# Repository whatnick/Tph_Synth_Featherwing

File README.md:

# 3-Phase ELV synthesizer using DAC and Opamps

This is an extra-low-voltage (ELV) FeatherWing using an MCP4728 four-channel,
12-bit I2C DAC with filtering and op-amp signal conditioning. The schematic
exposes three voltage outputs and one Howland current output, not three
independent voltage/current pairs. Host timing, output range and accuracy
require hardware validation; this is not a mains power source or a certified
meter calibrator.

## Background and availability

The original prototype is described in
[Simulating 3-phase AC for Energy Monitor testing (October 2017)](https://whatnicklife.blogspot.com/2017/10/simulating-3-phase-ac-for-energy.html).
It used a Teensy 3.2, MCP4728 and op-amp conditioning to test energy monitors.
Those historical results do not qualify the current v0.4 hardware.

The [Tindie listing](https://www.tindie.com/products/whatnick/3-phase-ac-synthesizer/)
was US$50 and out of stock when checked on 2026-11-08. See the
[market, lab TCO and NILM replay assessment](doc/synthesis-business-case.md)
for competing equipment, cost assumptions, research references and the
limitations of appliance-signature injection.
The matching Tindie blog-link update is tracked in
[issue #7](https://github.com/whatnick/Tph_Synth_Featherwing/issues/7);
publishing it requires authenticated seller access.

## KiCad 10 design

Revision **v0.4 (2026-10-28)** is maintained in
`Tph_Synth_Featherwing\Tph_Synth_Featherwing.kicad_pro`. Open that project and
its root schematic rather than treating the hierarchical sheets as separate
projects. The revision is also printed on the PCB bottom silkscreen.

The project-local symbol and footprint tables resolve the converted libraries,
board-edge silkscreen variants and existing `3dmodels` assets. Keep these
directories together with the project and install the standard KiCad 10
symbol, footprint and 3D-model libraries.

From the repository root, validate with KiCad 10's `kicad-cli` on `PATH`:

```powershell
kicad-cli sch erc .\Tph_Synth_Featherwing\Tph_Synth_Featherwing.kicad_sch --severity-all --exit-code-violations
kicad-cli pcb drc .\Tph_Synth_Featherwing\Tph_Synth_Featherwing.kicad_pcb --severity-all --schematic-parity --exit-code-violations
```

Both checks pass with zero violations, unconnected items or schematic-parity
mismatches. All 515 existing tracks/vias and component placement are preserved.
The Default and Power netclasses use 0.15 mm clearance; silkscreen-edge checking
is enabled. See [the v0.4 schematic](doc/v0.4/schematic.pdf) and
[top](doc/v0.4/board-top.png)/[bottom](doc/v0.4/board-bottom.png) renders and a
[populated STEP turntable](doc/v0.4/board-turntable.mp4) (Feather headers are
DNP and not shown). Recreate it by exporting a populated STEP with
`kicad-cli pcb export step --subst-models --include-tracks --include-pads
--include-silkscreen --include-soldermask`, converting it to GLB with the
`cascadio` Python package, then running
`blender -b --factory-startup -P scripts/render_turntable.py -- board.glb out.mp4 150 anim`.
The exact R10 PV36W STEP was unavailable, so R10 uses the generic 3296W model.
These are visualisations, not mechanical fit certification.
These CAD checks do not replace hardware/firmware and analog-output testing.

## Manufacturing preparation

The current preparation is in `manufacturing\v0.4`. **Assembly and purchasing
are on hold**, even though the CAD checks pass. Use the freshly generated
fabrication ZIP there, not the historical `Tph_Synth_Featherwing\gerbers`,
`bom` spreadsheet or iBOM. The archive has copper, mask, silkscreen, paste and
outline Gerbers plus separate PTH/NPTH drills. The nominal outline is
51 x 58.5 mm, two copper layers, 1.6 mm board thickness. Confirm material,
copper weight, surface finish, quantity and panelization with the fabricator.
The [ten-board Elecrow PCBA request](manufacturing/elecrow-pcba-2026-11-07/quote.json),
PN `20261107105421`, was submitted on 2026-11-07 and remains Pending Quotation
on the 2026-11-08 live check. Components are unpriced; US$88 plus separately
listed US$15.94 freight is not the final turnkey price. No payment or
production approval was made. The earlier bare-PCB cart entry is historical
and its absence does not establish a complete ordering history.

Generate a new package into an empty directory using KiCad's bundled Python:

```powershell
& 'C:\Program Files\KiCad\10.0\bin\python.exe' .\scripts\prepare_manufacture.py --output .\manufacturing\v0.4-new
```

The exporter requires zero ERC, DRC, unconnected and parity findings. It derives
the BOM from schematic fields, checks SMT placements against that BOM and
records input/output SHA-256 hashes in `manifest.json`. Regenerate into a new
directory if the destination is already populated; it deliberately refuses to
mix old and new exports. `release-status.json` records every sourcing review
and release action. Positions are in millimetres using the absolute CAD origin
for Gerbers, drills and placements; bottom X is not negated. Have the assembler
verify rotations, polarity and panel tooling. THT parts are listed separately
from the SMT position file.

For [issue #3](https://github.com/whatnick/Tph_Synth_Featherwing/issues/3),
SDA, SCL, 3V3, GND, VUSB and VBAT are labelled at the Feather header pads on
both PCB sides. Back-side labels are mirrored for correct fabrication.
Silkscreen checks enforce 0.15 mm clearance; test-pad references and the U4
reference are positioned clear of other markings. Run the tests with KiCad's
bundled Python to include the PCB pin-label and silkscreen-rule checks:

```powershell
& 'C:\Program Files\KiCad\10.0\bin\python.exe' -m unittest discover -s tests -v
```

Initial legacy sourcing evidence is in `sourcing\distributor-review-2026-11-07.json`
and copied into the manufacturing package. All 21 unique legacy fitted MPNs (46 parts,
22 BOM rows) were checked in three Mouser MCP batches; DigiKey was used for
four targeted blocker/candidate lookups. Results were matched by **MPN and
manufacturer**, excluding an unrelated obsolete ROHM `LM324PWR` result.
Prices are indicative USD single-unit observations, not a quotation or landed
cost. Null Mouser lifecycle means "not stated", not "Active".

The user-approved breakout replacements are now applied to the schematic,
PCB and review BOM, including legacy `manf#` fields:

| References | Selected MPN | Ratings/package | Stocked source observed 2026-11-07 |
|---|---|---|---|
| C1-C3 | TDK `C2012X5R1V226MT000E` | 22 uF, +/-20%, 35 V, X5R, 0805 | LCSC/JLCPCB `C338080`: 56,013 |
| C4-C11/C18 | Murata `GRM21BR61H106KE43L` | 10 uF, +/-10%, 50 V, X5R, 0805 | Mouser `81-GRM21BR61H106KE3L`: 2,564; JLCPCB `C440198`: 1,065,869 |
| C12 | YAGEO `CC0603BRNPO9BN5R0` | 5 pF, +/-0.1 pF, 50 V, C0G, 0603 | Mouser `603-CC603BRNPO9BN5R0`: 2,442 |

See `sourcing\distributor-review-substitutions-2026-11-07.json` for approval,
voltage rationale and current choices; the earlier review and alternative
records are historical. No voltage rating is reduced. The intended VBAT/5 V
and +/-5 V circuits are below these ratings; external overvoltage and fault
transients have not been qualified. Copper, placement and footprint geometry
are unchanged.

Remaining release checks:

- **Capacitor performance:** the 22 uF dielectric changes from JB to X5R.
  Check effective capacitance under DC bias/temperature, boost and charge-pump
  startup/ripple/stability, and 5 pF compensation on hardware. Murata's reference
  sheet is headed General Purpose, while DigiKey labels its application Mobile
  Devices Only; use is approved for this breakout, not unrestricted production.
  Keep the manufacturer application/height checks on the release checklist.
- **Supply/packing:** the TDK exact MPN is sourced through LCSC/JLCPCB, not
  presently orderable at Mouser or DigiKey. Recheck inventory before purchase.
  Observed Mouser stock of the replacements is below one full reel; verify
  packaging with the assembler and supplier rather than assuming reel supply.
- **R10:** verify `PV36W202C01B00` body/lead geometry, pin numbering and adjustment
  access against the Bourns 3296W footprint. This is an unverified fit, not a
  demonstrated mismatch: the PCB has three collinear holes on 2.54 mm centres,
  0.8 mm drills; pins 1/2 are connected and pin 3 is unused.
  The supplied `doc/pv36.pdf` now confirms inline pitch/pin order and pin 2
  as wiper, but recommends 0.9 mm holes rather than the PCB's 0.8 mm.
  Nominal lead diameter is 0.51 +/-0.03 mm; check finished-hole tolerances
  and insertion. R10's 3296W 3D model remains a proxy, not a verified PV36W.
- **Panel-pot CAD:** R7/R8/R9/RV1 use the Bourns PTV09A-2X20F family STEP.
  Corrected its model X offset from 3.5 to 3.1 mm to align signal leads.
  All lead/tab sections fit nominal holes at board midplane, but about
  0.331 mm3 model/board intersection remains per pot near mounting features;
  verify physical seating. See `sourcing\distributor-review-pot-fit-2026-11-07.json`
  for measurements, provenance and exact-MPN model-search limitations.
- **Host interface:** Adafruit
  [3200](https://www.adafruit.com/product/3200) is an external Teensy-to-Feather
  adapter, not a component fitted at MS1. It is listed separately from the PCB
  assembly BOM. **DNP the Feather host 12-pin/16-pin headers during
  manufacture.** Users fit compatible stacking headers later to suit their
  Feather; factory header selection/stacking height is not a release blocker.
  This policy applies only to the host rows, not fitted J2/J3 connectors.
  Headers and the Teensy are excluded from factory purchasing.
- **Production quantity/packaging:** R11-R14 consume four precision resistors
  per board; the 163 units observed at Mouser cover at most 40 boards before
  spares. U4 `MCP4728-E/UN` is supplied in tubes; assembler acceptance or a
  qualified reel suffix is still required.
- All other legacy MPNs still require datasheet electrical/mechanical
  qualification and a fresh stock, packaging, price and lifecycle check before
  ordering. Bench-test power rails, I2C/DAC, analog outputs and
  the Howland current source before a production release.

`Manufacturer`, `MPN`, `Description`, `DigiKey`, `Mouser`, `Assembly`,
`SourcingStatus` and `SourcingNotes` live on the schematic symbols and are
mirrored to the PCB for parity. `DigiKey` and `Mouser` remain **search URLs**.
Separate `MouserOrderCode`, `DigiKeyOrderCode`, `LCSCOrderCode` and `DistributorChecked` fields
carry dated, exact-manufacturer MCP observations; blank DigiKey codes mean
that MPN was not checked there. These codes do not override a sourcing hold.

The harness now connects to the public **pcbparts** MCP at
`https://pcbparts.dev/mcp`. `mouser_get_part` batches up to 10 part lookups;
`digikey_get_part` checks one MPN/order code at a time. Parametric catalog
search is provided by `jlc_search`, not the distributor lookup tools.
The hosted service shares a 1,000-request/day quota per distributor; do not
retry quota errors or check the whole BOM repeatedly in DigiKey. No API keys
are needed for this hosted endpoint. Self-hosting requires your own
[DigiKey developer API](https://developer.digikey.com/) and
[Mouser Search API](https://www.mouser.com/api-search/) credentials to enable
their lookups. Keep credentials outside the repository.

## Features :
- 50/60 Hz Frequency Selector ( Possibly just do it in software).
- Pot driven voltage Setting by controlling inverting-Opamp gain.
- Modified-Howland current source to simulate current clamp output.
- Pot driven current source using a tapped potentiometer attached to DAC output.
- Adjustable AC voltage outputs from nominal +/-5 V op-amp supplies; available
  swing depends on headroom and load, and is not a +/-5 V RMS specification.
- Dual-voltage rail generation using [LM2663](https://au.element14.com/texas-instruments/lm2663mx-nopb/dc-dc-charge-pump-inverting-soic/dp/3008264) to flip 5v input to -5v.
- Boost-converter to push battery voltage (4.2v-3.7v) to 5v for non-USB power mode using [PAM2401](https://au.mouser.com/datasheet/2/115/PAM2401-347378.pdf).
- I2C DAC circuit to generate phase-shifted sine waves, as described in the
  [original prototype blog post](https://whatnicklife.blogspot.com/2017/10/simulating-3-phase-ac-for-energy.html),
  using [MCP4728](https://au.element14.com/microchip/mcp4728-e-un/ic-dac-12bit-quad-10msop/dp/1800217).
- Fully open-source schematic/pcb in KiCAD.

## Roadmap Features :
- Keep this board ELV-only; qualify output limits and provide repeatable
  low-voltage teaching and meter-front-end test procedures.
- Evaluate USB/battery power-path improvements within the ELV design envelope.
- Add I2C digital pots instead of physical pots.

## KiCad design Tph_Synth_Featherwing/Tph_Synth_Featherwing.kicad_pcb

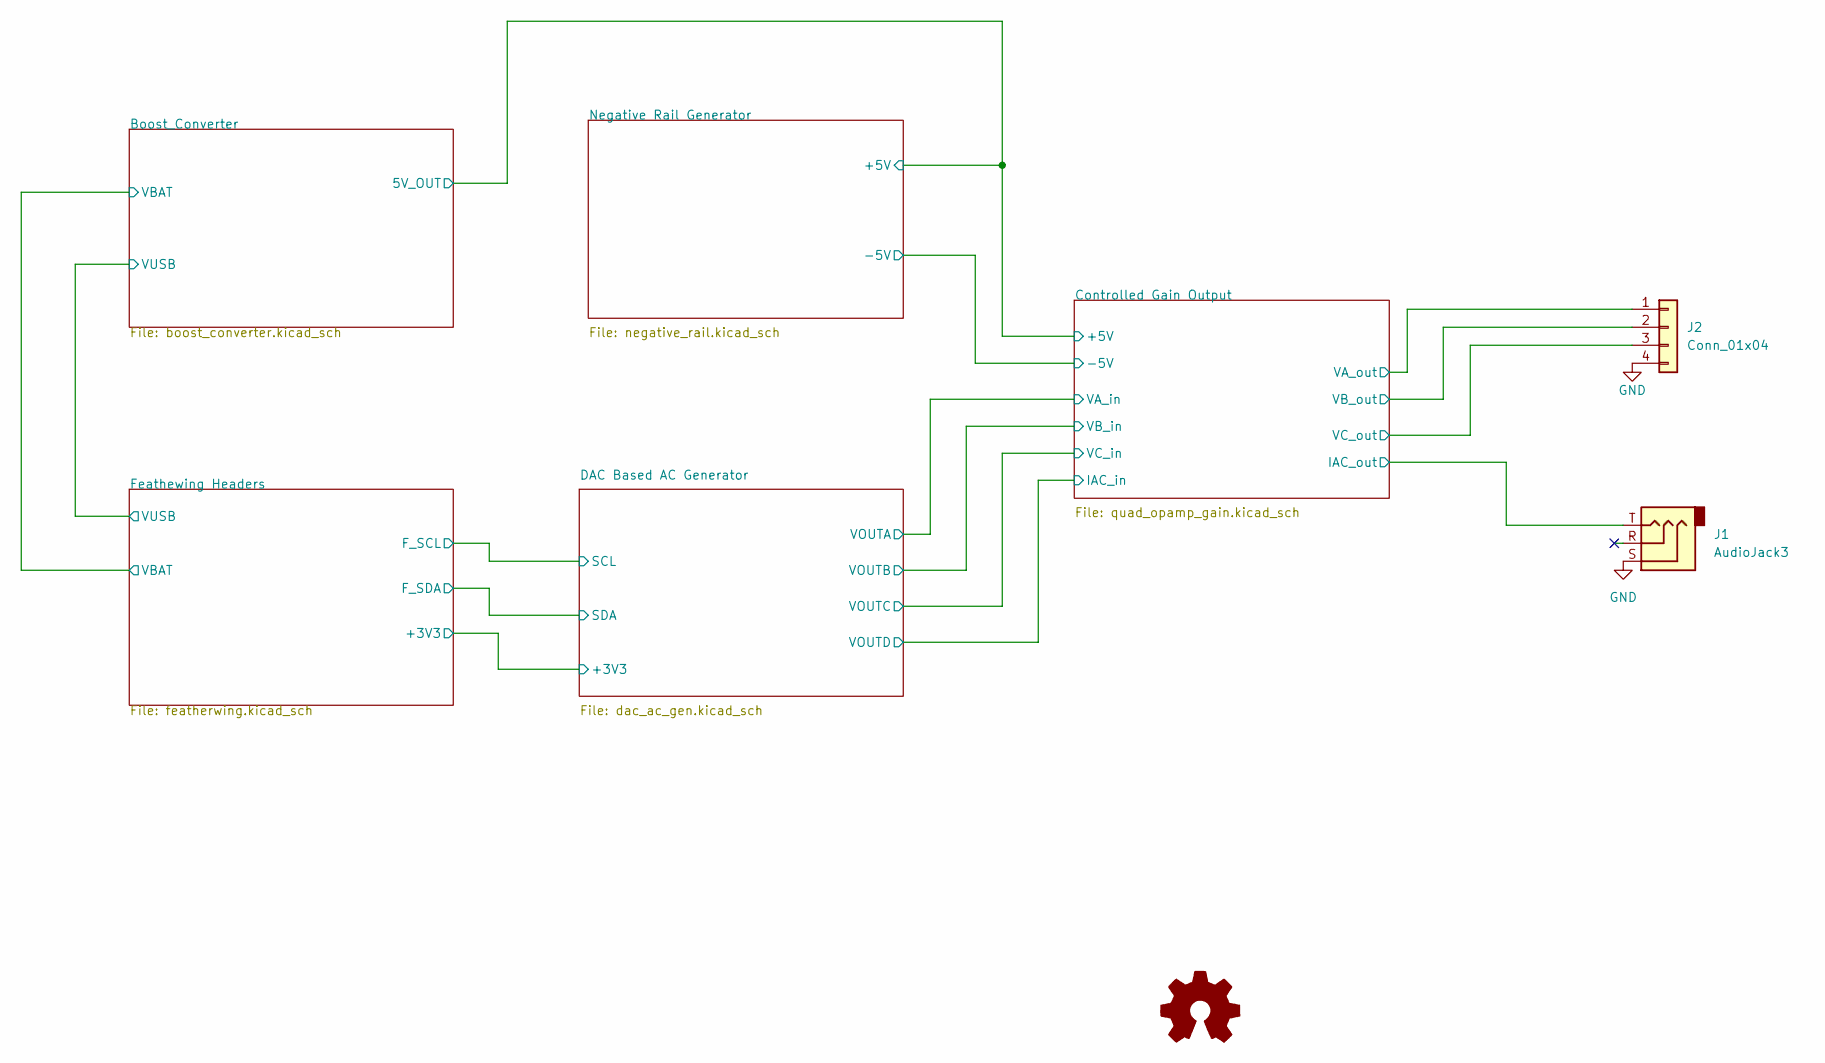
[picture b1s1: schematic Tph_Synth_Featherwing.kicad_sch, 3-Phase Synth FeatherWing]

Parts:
J1: AudioJack3; Jack_3.5mm_CUI_SJ-3523-SMT_Horizontal_EdgeMounted; MPN SJ-3523-SMT-TR; MouserOrderCode 490-SJ-3523-SMT-TR
J2: Conn_01x04; Molex_Nano-Fit_105314-xx04_2x02_P2.50mm_Horizontal_EdgeMoun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; MPN 105314-1204; MouserOrderCode 538-105314-1204
LOGO1: Logo_Open_Hardware_Small; OSHW-Logo2_7.3x6mm_SilkScreen

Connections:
/Controlled Gain Output/IAC_out: J1.T; also elsewhere on the board
/Controlled Gain Output/VA_out: J2.1; also elsewhere on the board
/Controlled Gain Output/VB_out: J2.2; also elsewhere on the board
/Controlled Gain Output/VC_out: J2.3; also elsewhere on the board
GND: J1.S, J2.4; also elsewhere on the board

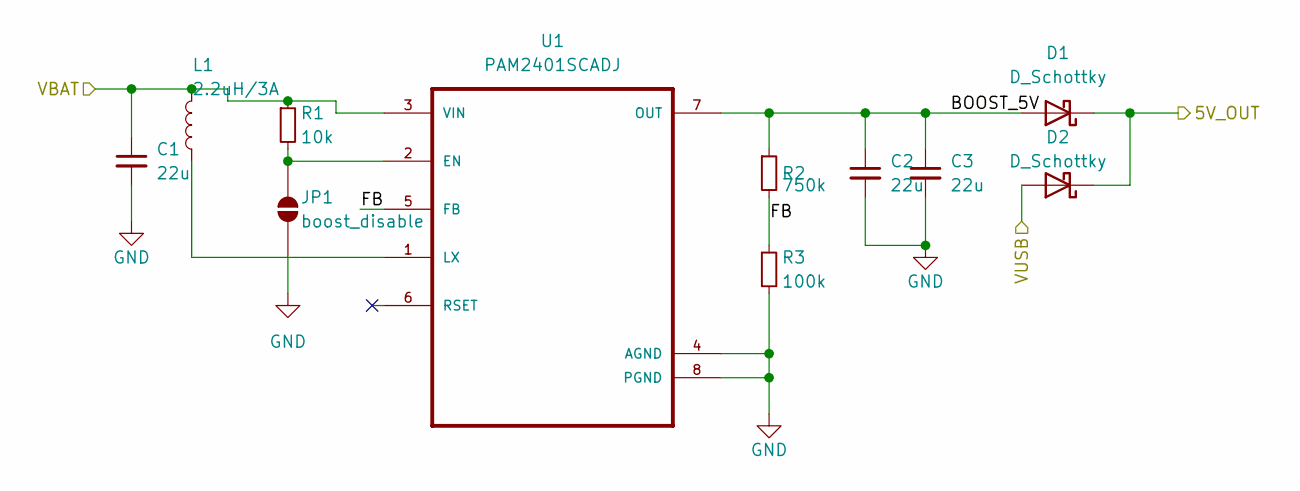
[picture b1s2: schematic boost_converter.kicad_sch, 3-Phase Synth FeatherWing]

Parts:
C1, C2, C3: 22u; C_0805_2012Metric; MPN C2012X5R1V226MT000E; LCSCOrderCode C338080
D1, D2: D_Schottky; D_SMB; MPN B330B-13-F; MouserOrderCode 621-B330B-F
JP1: boost_disable; SolderJumper-2_P1.3mm_Open_TrianglePad1.0x1.5mm
L1: 2.2uH/3A; L_Bourns-SRR1005_ProjectModel; MPN SRR1005-2R2M; MouserOrderCode 652-SRR1005-2R2M
R1: 10k; R_0603_1608Metric; MPN RT0603FRD0710KL; MouserOrderCode 603-RT0603FRD0710KL
R2: 750k; R_0603_1608Metric; MPN RC0603FR-07750KL; MouserOrderCode 603-RC0603FR-07750KL
R3: 100k; R_0603_1608Metric; MPN RC0603FR-07100KL; MouserOrderCode 603-RC0603FR-07100KL
U1: PAM2401SCADJ; MSOP-8_3x3mm_P0.65mm; MPN PAM2401SCADJ; MouserOrderCode 621-PAM2401SCADJ

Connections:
+5V: D1.1 (K), D2.1 (K); also elsewhere on the board
/Boost_Converter/BOOST_5V: C2.1, C3.1, D1.2 (A), R2.1, U1.7 (OUT)
/Boost_Converter/FB: R2.2, R3.1, U1.5 (FB)
/Boost_Converter/VBAT: C1.1, L1.2, R1.1, U1.3 (VIN); also elsewhere on the board
/Boost_Converter/VUSB: D2.2 (A); also elsewhere on the board
GND: C1.2, C2.2, C3.2, JP1.2 (B), R3.2, U1.4 (AGND), U1.8 (PGND); also elsewhere on the board
unnamed: JP1.1 (A), R1.2, U1.2 (EN)
unnamed: L1.1, U1.1 (LX)

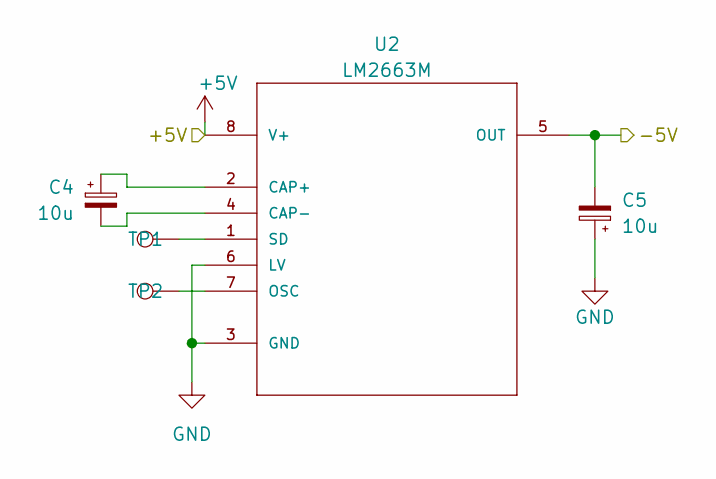
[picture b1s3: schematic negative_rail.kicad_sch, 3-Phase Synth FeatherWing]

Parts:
C4, C5: 10u; C_0805_2012Metric; MPN GRM21BR61H106KE43L; DigiKeyOrderCode 490-18663-1-ND
TP1, TP2: TestPoint; TestPoint_Pad_D1.0mm
U2: LM2663M; SOIC-8_3.9x4.9mm_P1.27mm; MPN LM2663MX/NOPB; MouserOrderCode 926-LM2663MX/NOPB

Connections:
+5V: U2.8 (V+); also elsewhere on the board
/Controlled Gain Output/-5V: C5.2, U2.5 (OUT); also elsewhere on the board
GND: C5.1, U2.3 (GND), U2.6 (LV); also elsewhere on the board
unnamed: C4.1, U2.2 (CAP+)
unnamed: C4.2, U2.4 (CAP-)
unnamed: TP2.1, U2.7 (OSC)
unnamed: TP1.1, U2.1 (SD)

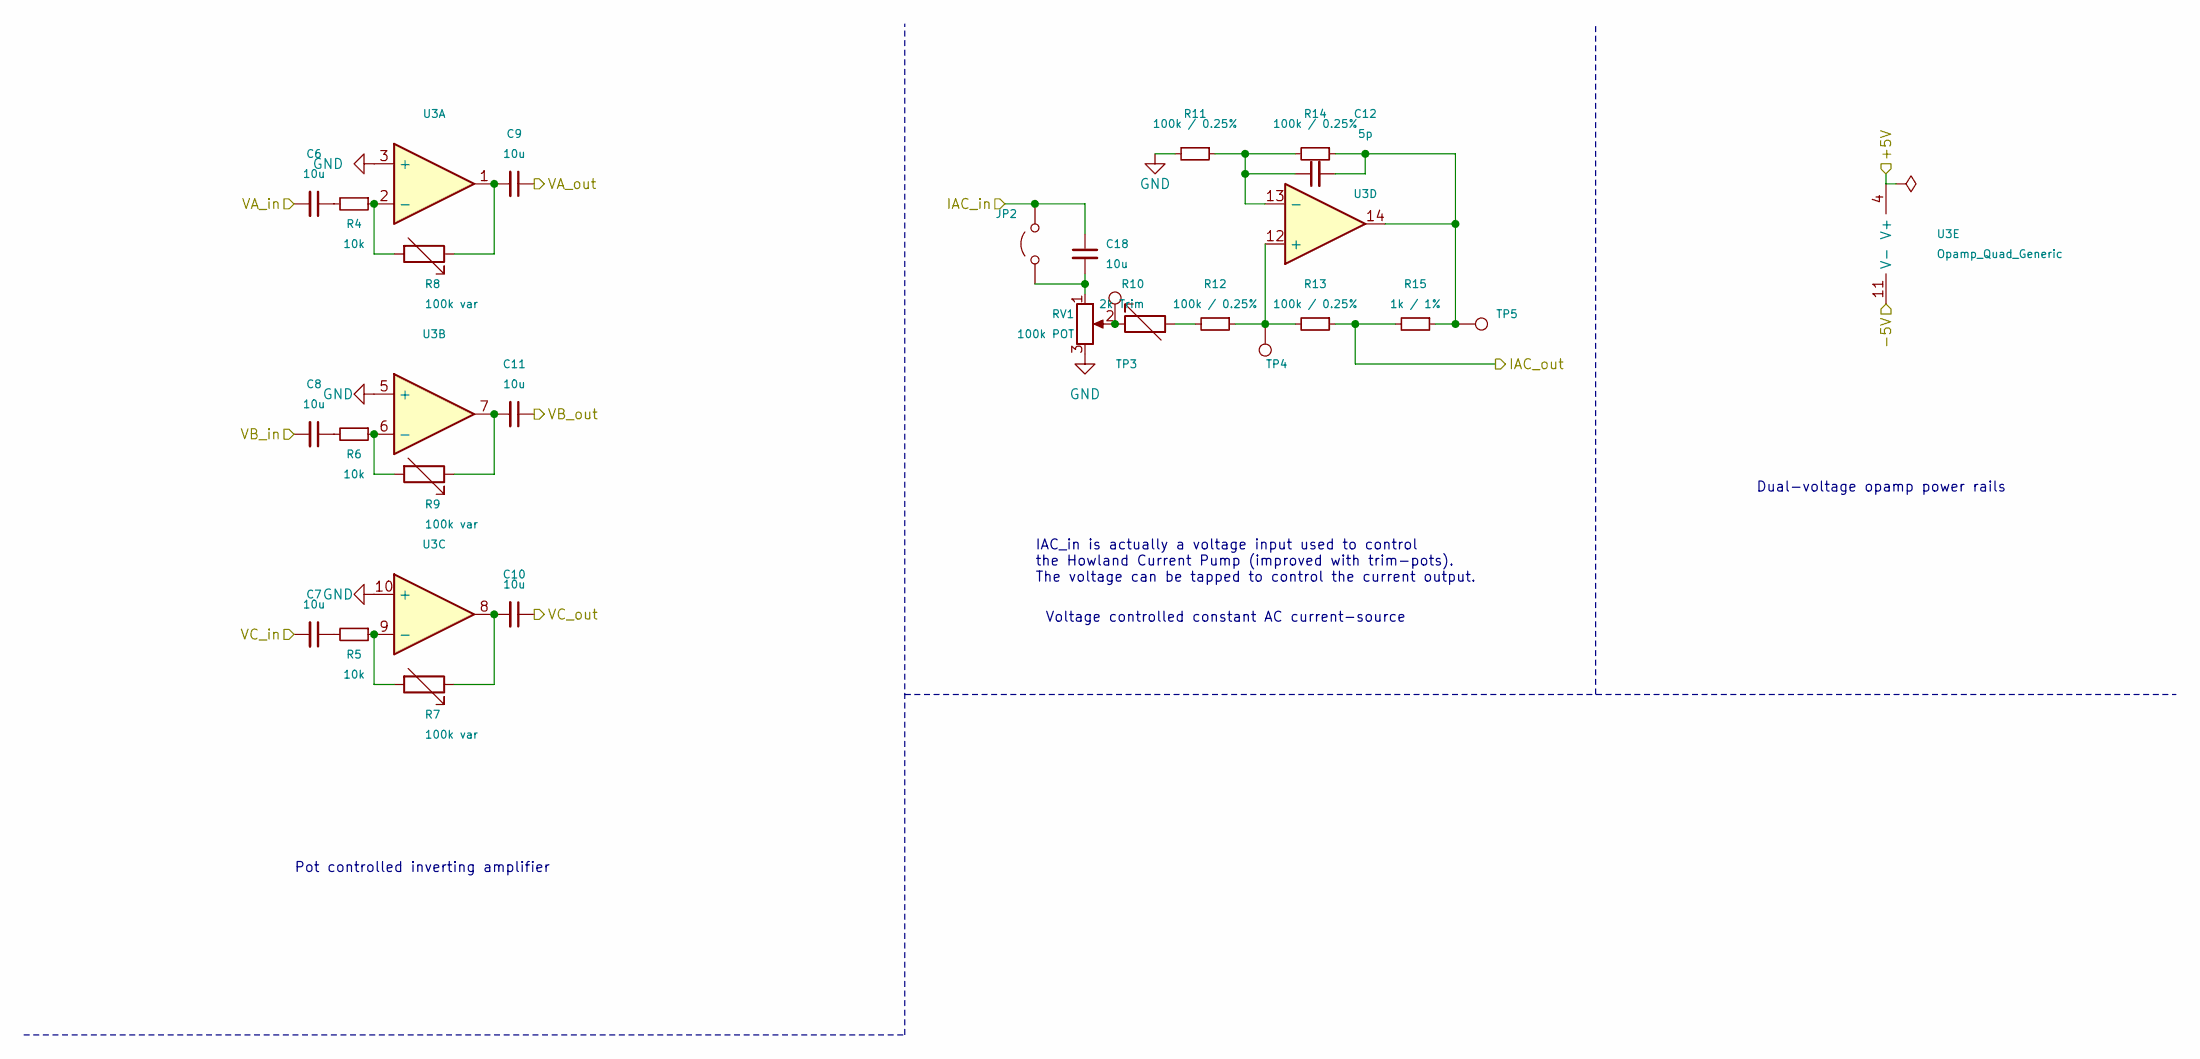
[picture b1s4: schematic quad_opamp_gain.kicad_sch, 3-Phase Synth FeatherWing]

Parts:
C6, C7, C8, C9, C10, C11, C18: 10u; C_0805_2012Metric; MPN GRM21BR61H106KE43L; DigiKeyOrderCode 490-18663-1-ND
C12: 5p; C_0603_1608Metric; MPN CC0603BRNPO9BN5R0; DigiKeyOrderCode 13-CC0603BRNPO9BN5R0CT-ND
JP2: Jumper_2_Open; SolderJumper-2_P1.3mm_Open_TrianglePad1.0x1.5mm
R4, R5, R6: 10k; R_0603_1608Metric; MPN RT0603FRD0710KL; MouserOrderCode 603-RT0603FRD0710KL
R7, R8, R9: 100k var; Potentiometer_Bourns_PTV09A-2_Single_Horizontal_EdgeMounted; MPN PTV09A-2020F-B104; MouserOrderCode 652-PTV09A-2020FB104
R10: 2k Trim; Potentiometer_Bourns_3296W_Vertical; MPN PV36W202C01B00; MouserOrderCode 81-PV36W202C01B00
R11, R12, R13, R14: 100k / 0.25%; R_0603_1608Metric; MPN RT0603CRE07100KL; MouserOrderCode 603-RT0603CRE07100KL
R15: 1k / 1%; R_0603_1608Metric; MPN CRT0603-FY-1001ELF; MouserOrderCode 652-CRT0603FY1001ELF
RV1: 100k POT; Potentiometer_Bourns_PTV09A-2_Single_Horizontal_EdgeMounted; MPN PTV09A-2020F-B104; MouserOrderCode 652-PTV09A-2020FB104
TP3, TP4, TP5: TestPoint; TestPoint_Pad_D1.0mm
U3: Opamp_Quad_Generic; TSSOP-14_4.4x5mm_P0.65mm; MPN LM324PWR; MouserOrderCode 595-LM324PWR

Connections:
+5V: U3.4 (V+); also elsewhere on the board
/Controlled Gain Output/-5V: U3.11 (V-); also elsewhere on the board
/Controlled Gain Output/IAC_in: C18.1, JP2.2 (B); also elsewhere on the board
/Controlled Gain Output/IAC_out: R13.1, R15.2; also elsewhere on the board
/Controlled Gain Output/VA_in: C6.2; also elsewhere on the board
/Controlled Gain Output/VA_out: C9.1; also elsewhere on the board
/Controlled Gain Output/VB_in: C8.2; also elsewhere on the board
/Controlled Gain Output/VB_out: C11.1; also elsewhere on the board
/Controlled Gain Output/VC_in: C7.2; also elsewhere on the board
/Controlled Gain Output/VC_out: C10.1; also elsewhere on the board
GND: R11.2, RV1.3, U3.3 (+), U3.5 (+), U3.10 (+); also elsewhere on the board
unnamed: C6.1, R4.2
unnamed: C7.1, R5.2
unnamed: C8.1, R6.2
unnamed: C9.2, R8.1, U3.1
unnamed: C10.2, R7.1, U3.8
unnamed: C11.2, R9.1, U3.7
unnamed: C12.2, R14.1, R15.1, TP5.1, U3.14
unnamed: C18.2, JP2.1 (A), RV1.1
unnamed: R10.1, RV1.2, TP3.1
unnamed: R10.2, R12.2
unnamed: R4.1, R8.2, U3.2 (-)
unnamed: R6.1, R9.2, U3.6 (-)
unnamed: R5.1, R7.2, U3.9 (-)
unnamed: R12.1, R13.2, TP4.1, U3.12 (+)
unnamed: C12.1, R11.1, R14.2, U3.13 (-)

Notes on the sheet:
Voltage controlled constant AC current-source
Pot controlled inverting amplifier
IAC_in is actually a voltage input used to control the Howland Current Pump (improved with trim-pots). The voltage can be tapped to control the current output.
Dual-voltage opamp power rails

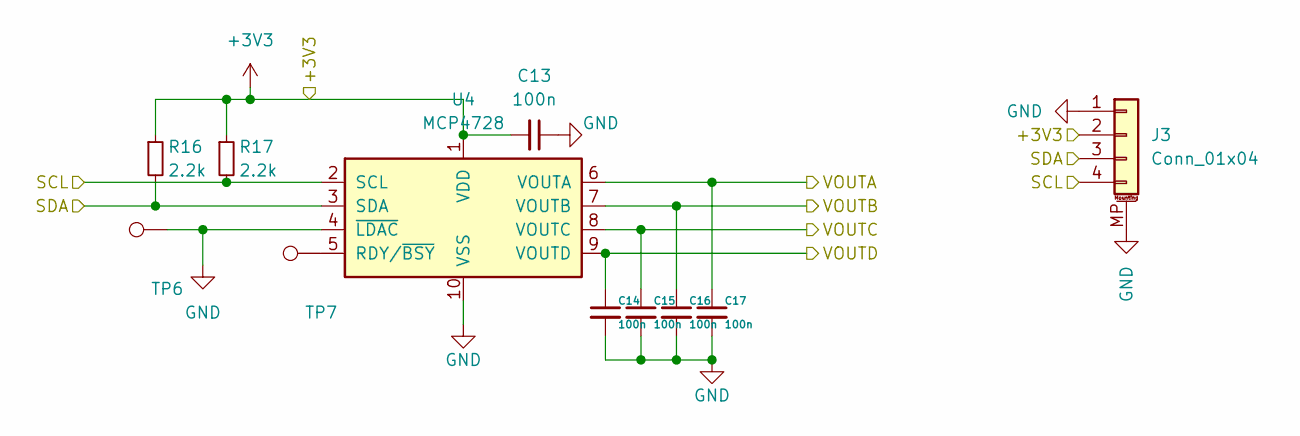
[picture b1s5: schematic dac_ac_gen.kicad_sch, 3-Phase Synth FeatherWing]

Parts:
C13, C14, C15, C16, C17: 100n; C_0603_1608Metric; MPN GCM188L81H104KA57D; MouserOrderCode 81-GCM188L81H104KA7D
J3: Conn_01x04; JST_SH_SM04B-SRSS-TB_1x04-1MP_P1.00mm_Horizontal; MPN SM04B-SRSS-TB(LF)(SN); MouserOrderCode 306-SM04BSRSSTBLFSN
R16, R17: 2.2k; R_0603_1608Metric; MPN RC0603FR-072K2L; MouserOrderCode 603-RC0603FR-072K2L
TP6, TP7: TestPoint; TestPoint_Pad_D1.0mm
U4: MCP4728; MSOP-10_3x3mm_P0.5mm; MPN MCP4728-E/UN; MouserOrderCode 579-MCP4728-E/UN

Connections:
+3V3: C13.2, J3.2, R16.1, R17.1, U4.1 (VDD); also elsewhere on the board
/Controlled Gain Output/IAC_in: C14.1, U4.9 (VOUTD); also elsewhere on the board
/Controlled Gain Output/VA_in: C17.1, U4.6 (VOUTA); also elsewhere on the board
/Controlled Gain Output/VB_in: C16.1, U4.7 (VOUTB); also elsewhere on the board
/Controlled Gain Output/VC_in: C15.1, U4.8 (VOUTC); also elsewhere on the board
/DAC Based AC Generator/SCL: J3.4, R17.2, U4.2 (SCL); also elsewhere on the board
/DAC Based AC Generator/SDA: J3.3, R16.2, U4.3 (SDA); also elsewhere on the board
GND: C13.1, C14.2, C15.2, C16.2, C17.2, J3.1, J3.MP (MountPin), TP6.1, U4.4 (~LDAC), U4.10 (VSS); also elsewhere on the board
unnamed: TP7.1, U4.5 (RDY/~BSY)

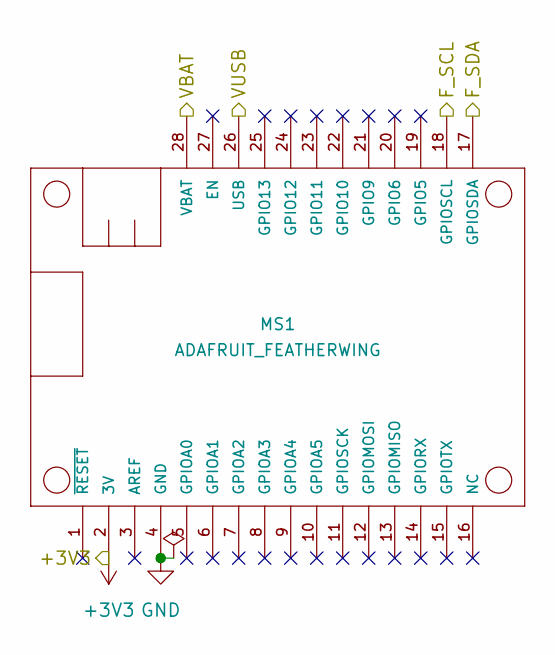
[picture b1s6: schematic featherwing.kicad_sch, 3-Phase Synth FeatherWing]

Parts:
MS1: ADAFRUIT_FEATHERWING; adafruit_featherwing_HostOutlineOnFab; MPN 3200

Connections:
+3V3: MS1.2 (3V); also elsewhere on the board
/Boost_Converter/VBAT: MS1.28 (VBAT); also elsewhere on the board
/Boost_Converter/VUSB: MS1.26 (USB); also elsewhere on the board
/DAC Based AC Generator/SCL: MS1.18 (GPIOSCL); also elsewhere on the board
/DAC Based AC Generator/SDA: MS1.17 (GPIOSDA); also elsewhere on the board
GND: MS1.4 (GND); also elsewhere on the board

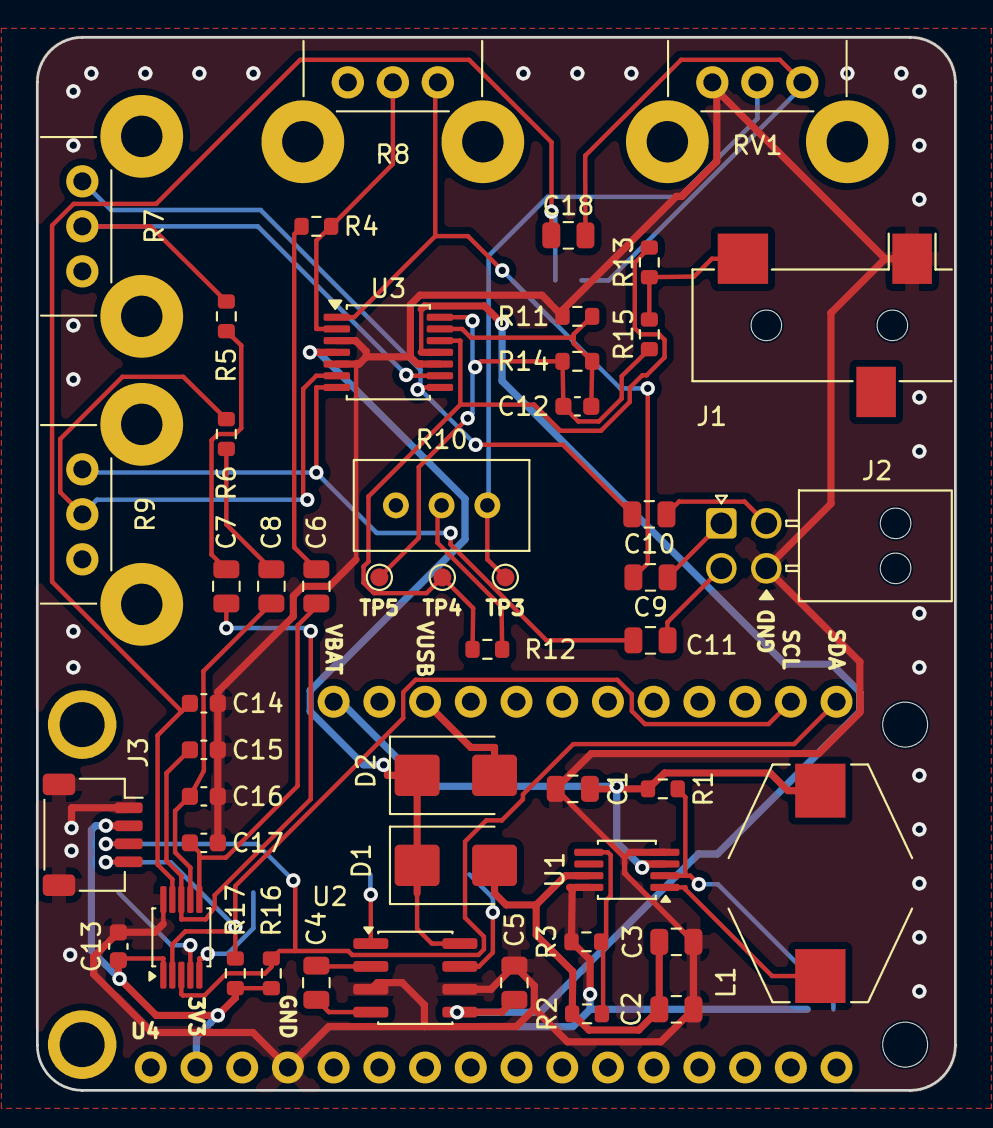
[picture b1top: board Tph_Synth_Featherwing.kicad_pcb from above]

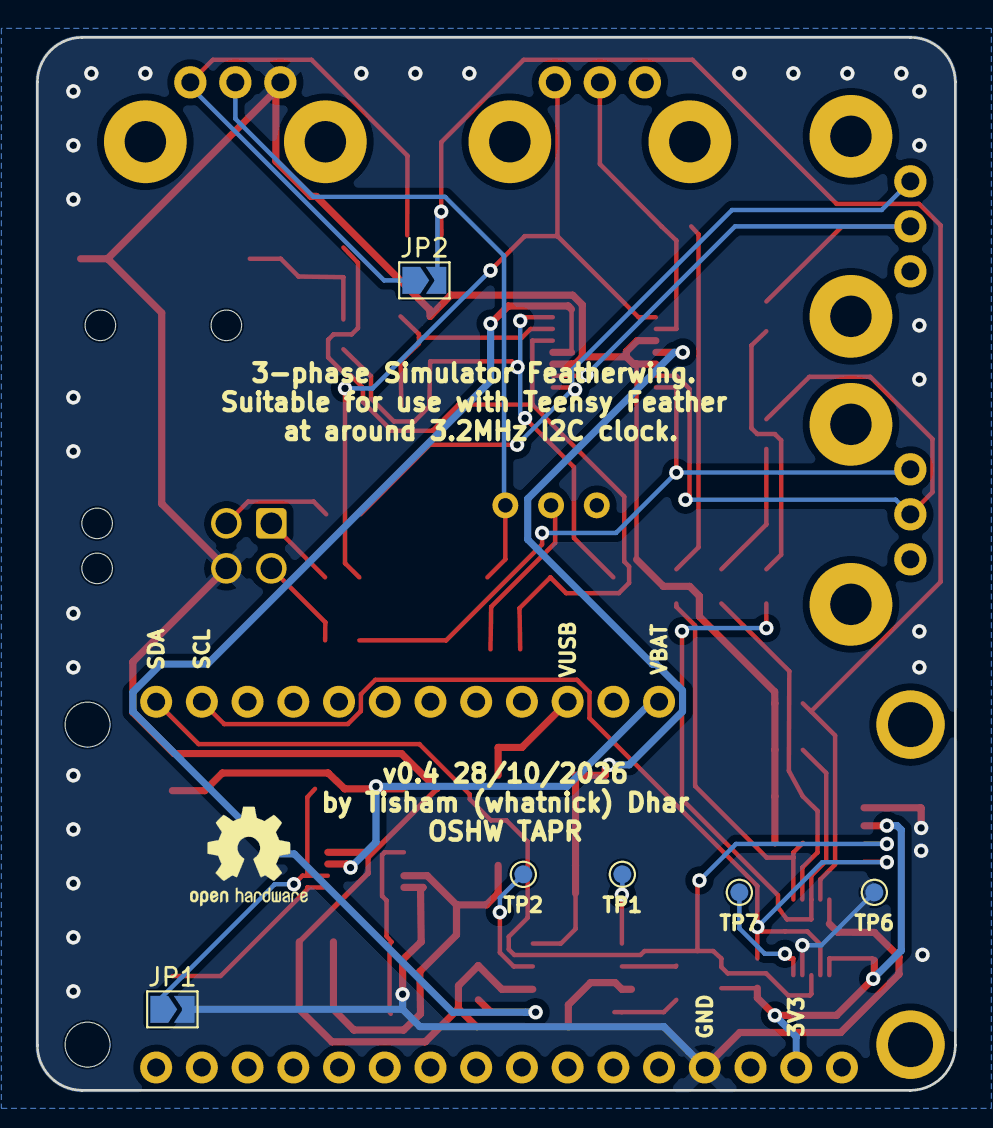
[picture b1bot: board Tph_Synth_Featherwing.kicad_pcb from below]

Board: 2 copper layers, 51.0 x 58.5 mm, 57 parts (7 on the bottom side), 40 nets.

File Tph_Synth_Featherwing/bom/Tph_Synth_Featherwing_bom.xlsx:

References | manf# | Value | Footprint | Quantity
C1, C2, C3 | C2012JB1V226M125AC | 22u | C_0805_2012Metric | 3
C13, C14, C15, C16, C17 | GCM188L81H104KA57D | 100n | C_0603_1608Metric | 5
C12 | GJM0335C1E5R0BB01D | 5p | C_0603_1608Metric | 1
C4, C5, C6, C7, C8, C9, C10, C11, C18 | GMK212BBJ106MG-T | 10u | C_0805_2012Metric | 9
R15 | CRT0603-FY-1001ELF | 1k / 1% | R_0603_1608Metric | 1
R7, R8, R9 | PTV09A-2020F-B104 | 100k var | Potentiometer_Bourns_PTV09A-2_Single_Horizontal | 3
R10 | PV36W202C01B00 | 2k Trim | Potentiometer_Bourns_3296W_Vertical | 1
R3 | RC0603FR-07100KL | 100k | R_0603_1608Metric | 1
R16, R17 | RC0603FR-072K2L | 2.2k | R_0603_1608Metric | 2
R2 | RC0603FR-07750KL | 750k | R_0603_1608Metric | 1
R11, R12, R13, R14 | RT0603CRE07100KL | 100k / 0.25% | R_0603_1608Metric | 4
R1, R4, R5, R6 | RT0603FRD0710KL | 10k | R_0603_1608Metric | 4
L1 | SRR1005-2R2M | 2.2uH/3A | L_Bourns-SRR1005 | 1
D1, D2 | B330B-13-F | D_Schottky | D_SMB | 2
U2 | LM2663MX/NOPB | LM2663M | SOIC-8_3.9x4.9mm_P1.27mm | 1
U3 | LM324PWR | Opamp_Quad_Generic | TSSOP-14_4.4x5mm_P0.65mm | 1
U4 | MCP4728-E/UN | MCP4728 | MSOP-10_3x3mm_P0.5mm | 1
U1 | PAM2401SCADJ | PAM2401SCADJ | MSOP-8_3x3mm_P0.65mm | 1
MS1 | 3200 | ADAFRUIT_FEATHERWING | adafruit_featherwing | 1
RV1 | PTV09A-2020F-B104 | 100k POT | Potentiometer_Bourns_PTV09A-2_Single_Horizontal | 1
J2 | 105314-1204 | Conn_01x04 | Molex_Nano-Fit_105314-xx04_2x02_P2.50mm_Horizontal | 1
J1 | SJ-3523-SMT-TR | AudioJack3 | Jack_3.5mm_CUI_SJ-3523-SMT_Horizontal | 1
J3 | SM04B-SRSS-TB(LF)(SN) | Conn_01x04 | JST_SH_SM04B-SRSS-TB_1x04-1MP_P1.00mm_Horizontal | 1

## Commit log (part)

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2019-11-13 Initial Roadmap
2019-11-13 Initial Hierarchial sheets
2019-11-13 Initial part selection and Changelog
2019-11-13 Add LM2663 Negative voltage generator
2019-12-08 Add parts for DAC
2019-12-08 Add parts for voltage inverter
2019-12-14 Progress on sub-sheet labels and boost converter
2019-12-15 Boost-converter and inverting opamps
2019-12-15 Added first-cut of schematic
2019-12-16 Changelog and Readme updates
2019-12-16 240v is technically LV
2019-12-17 Initial attempt at PCB
2019-12-18 Initial cut at part placement
2019-12-18 Note Inductor parts choice
2019-12-18 Update changelog
2019-12-19 Pre-lim autoroute and renders
2019-12-19 More don't trust the autorouter
2019-12-19 Change 3D model colour, rounded corners
2019-12-20 Added ground pour and stitching vias
2019-12-20 New renders with ground pour
2019-12-20 Add blurb silk screen
2019-12-20 Add PCB measurements
2019-12-20 Add gerbers for v0.1
2019-12-22 Added BOM and upgraded to kicad 5.0
2019-12-22 Add Excel BOM for quick upload to suppliers
2020-02-01 #1 and #2 add mising wiring
2020-02-01 #1 and #2 Generate new gerbers and bom
2020-02-01 Clean up old gerbers
2020-12-19 Migrate to KiCAD nightly
2020-12-19 Fix silk screens
2020-12-19 Add Qwiic connector to design
2020-12-19 Improve/update silk screen
2020-12-19 New gerbers
2020-12-19 Update Excel BOM
2022-02-10 Upgrade to kicad 6
